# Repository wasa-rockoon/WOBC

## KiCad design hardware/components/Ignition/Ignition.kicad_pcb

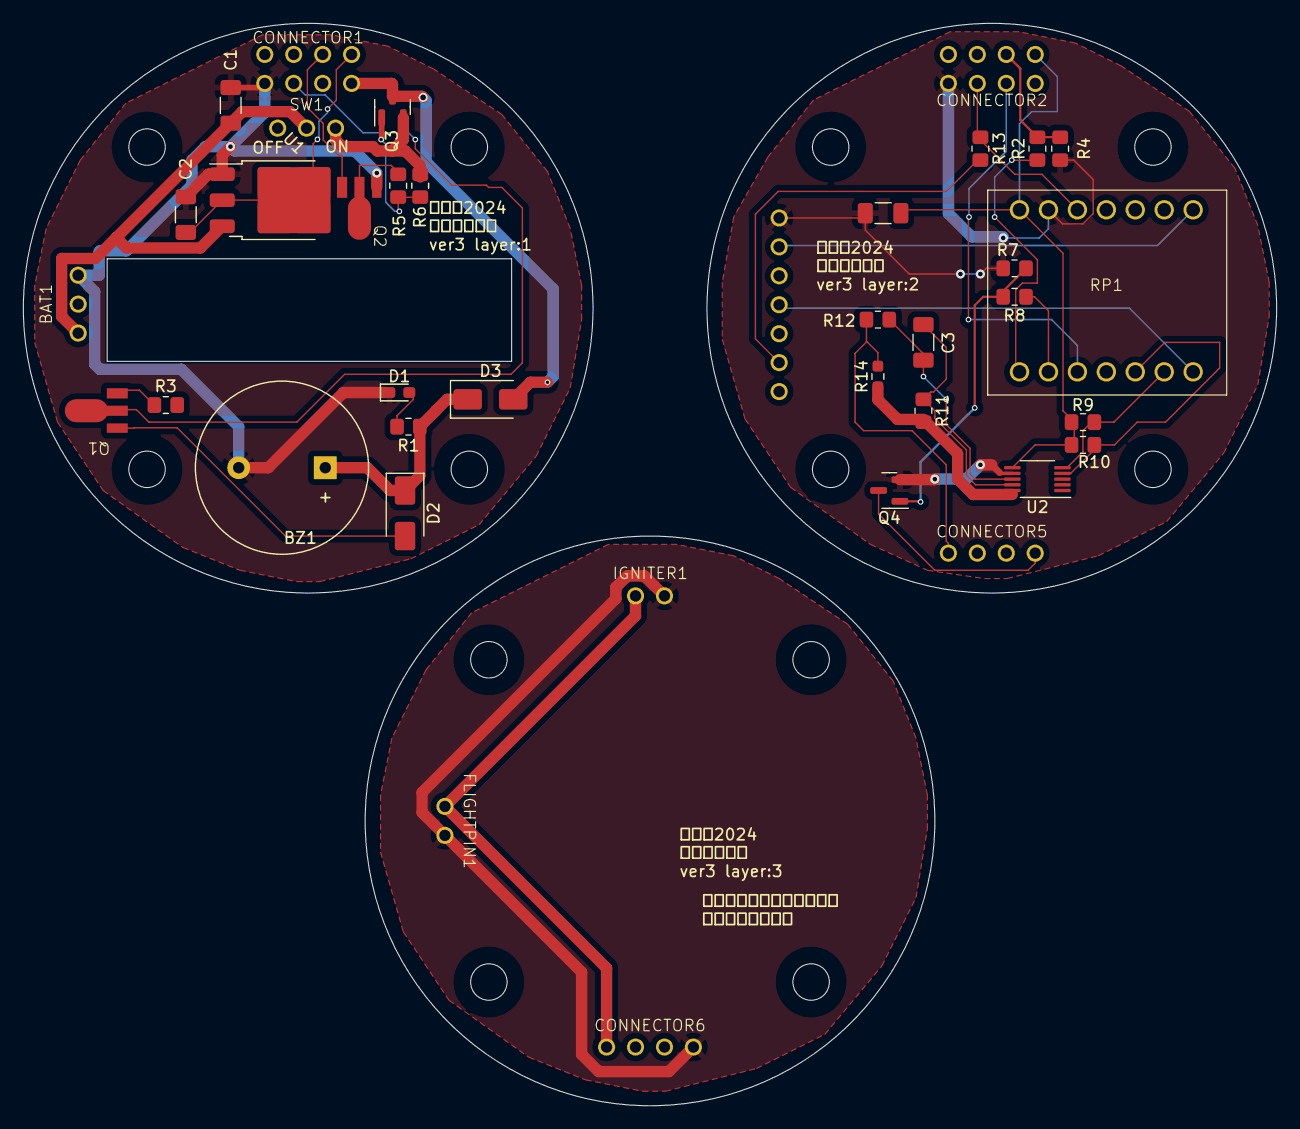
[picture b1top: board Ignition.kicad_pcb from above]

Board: 2 copper layers, 110.0 x 95.0 mm, 38 parts (0 on the bottom side), 33 nets.

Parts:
BAT1: 3pin_connector
BZ1: Buzzer; Buzzer_15x7.5RM7.6
C1, C2: 10μF; C_1206_3216Metric_Pad1.33x1.80mm_HandSolder
C3, C4: 0.1u; C_1206_3216Metric_Pad1.33x1.80mm_HandSolder
CONNECTOR1, CONNECTOR2: 8pin_looseconnector
CONNECTOR5, CONNECTOR6: 4pin_looseconnector
D1: LED; LED_0603_1608Metric_Pad1.05x0.95mm_HandSolder
D2, D3: US1M; D_SMA
FLIGHTPIN1: 2pin_connector
IGNITER1: 2pin_connector
Q1, Q2: NPN; npn
Q3: AO3401A; SOT-23
Q4: 2N7002; SOT-23
R1: 470; R_0805_2012Metric_Pad1.20x1.40mm_HandSolder
R2, R3, R7: 1000; R_0805_2012Metric_Pad1.20x1.40mm_HandSolder
R4, R6, R9, R10, R13: 10000; R_0805_2012Metric_Pad1.20x1.40mm_HandSolder
R5: 510; R_0805_2012Metric_Pad1.20x1.40mm_HandSolder
R8: 100; R_0805_2012Metric_Pad1.20x1.40mm_HandSolder
R11, R12: 4.7; R_0805_2012Metric_Pad1.20x1.40mm_HandSolder
R14: 0.002; R_0603_1608Metric_Pad0.98x0.95mm_HandSolder
RP1: SeeedXiaoRP2040
SW1: SW_DPDT_x2; SW
TWE1: TWELITE
U1: LM2940; TO-252-3_TabPin2
U2: INA226; VSSOP-10_3x3mm_P0.5mm

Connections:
/3V3_1: CONNECTOR1.7, Q1.1 (C)
/3V3_2: CONNECTOR2.7, R13.1, RP1.3 (3V3)
/ALART2: CONNECTOR2.6, RP1.12 (28)
/BAT1: Q3.2 (S), R6.1, SW1.3 (C)
/BAT1Z: CONNECTOR1.5, D3.2 (A), Q3.3 (D)
/BAT2: R11.2, R14.1, U2.10 (Vin+)
/BAT+: BAT1.1, C1.1, SW1.2 (B), U1.3 (I)
/GND1: BAT1.2, BZ1.2 (+), C1.2, C2.2, CONNECTOR1.8, D1.1 (K), Q2.3 (E), U1.1 (GND)
/GND2: C4.2, CONNECTOR2.8, Q4.2 (S), R4.2, R7.2, RP1.2 (GND), TWE1.1 (GND), U2.7 (GND)
/GND4: CONNECTOR6.4, FLIGHTPIN1.2, IGNITER1.2
/IGNITE+1: CONNECTOR1.3, Q2.2 (B)
/IGNITE+2: CONNECTOR2.3, R2.2, R4.1
/IGNITE-2: Q4.1 (G), R7.1, R8.2
/POW: C4.1, CONNECTOR2.4, R9.2, R10.2, RP1.1 (5V), U2.6 (VS)
/RX: RP1.7 (1), TWE1.2 (TXD)
/SCL: R9.1, RP1.9 (7), U2.5 (SCL)
/SDA: R10.1, RP1.10 (6), U2.4 (SDA)
/TX: RP1.8 (0), TWE1.4 (RXD)
unnamed: BZ1.1 (-), D2.1 (K), D3.1 (K), R1.1
unnamed: CONNECTOR5.1, R12.2, R14.2
unnamed: CONNECTOR6.1, FLIGHTPIN1.1, IGNITER1.1
unnamed: D1.2 (A), R1.2
unnamed: D2.2 (A), Q1.3 (E)
unnamed: Q1.2 (B), R3.1
unnamed: Q2.1 (C), R5.2
unnamed: Q3.1 (G), R5.1, R6.2
unnamed: CONNECTOR5.4, Q4.3 (D)
unnamed: R2.1, RP1.14 (26)
unnamed: R8.1, RP1.13 (27)
unnamed: R13.2, TWE1.6 (VCC)
unnamed: C2.1, CONNECTOR1.4, U1.2 (Q)
unnamed: C3.2, R12.1, U2.8 (Vbus)
unnamed: C3.1, R11.1, U2.9 (Vin-)

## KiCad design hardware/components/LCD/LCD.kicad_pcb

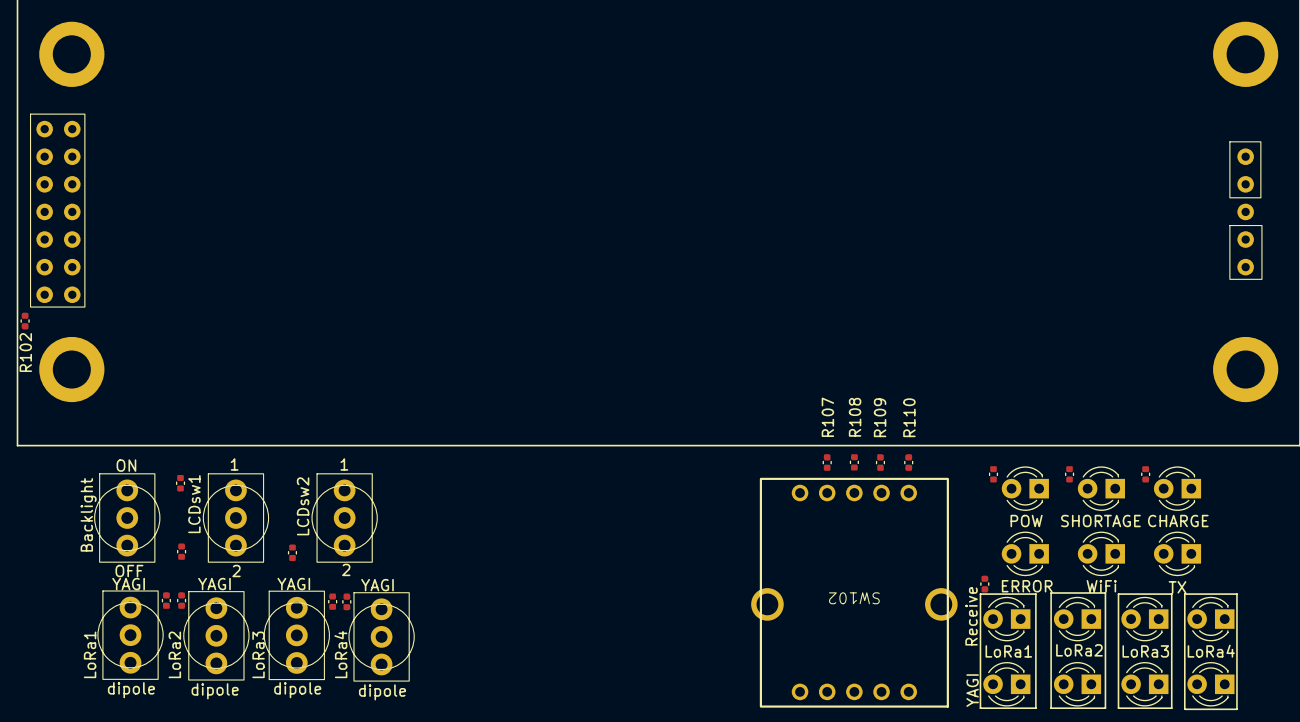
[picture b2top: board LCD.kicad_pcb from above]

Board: 2 copper layers, 40 parts (1 on the bottom side), 23 nets, no tracks yet.

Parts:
D101, D102, D103, D104, D105, D106, D107, D108, D109, D110, D111, D112, D113, D114: LED; LED_D3.0mm_FlatTop
J101: Conn_01x04_MountingPin; Grove_4P_L_SMD
R101, R107, R108, R109, R110, R111, R112, R113, R114, R115, R116: 47k; C_0402_1005Metric
R102, R103, R104, R105, R106: 1k; C_0402_1005Metric
SW101, SW103, SW104, SW105, SW106, SW107, SW108: sw1; ToggleSwitch
SW102: RotarySwitch_2x04
lcd101: SC2004CSWB-XA-LB-G; SC2004CSWB

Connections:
/LoRaSW1: R113.2, SW105.2 (B)
/LoRaSW2: R114.2, SW106.2 (B)
/LoRaSW3: R115.2, SW103.2 (B)
/LoRaSW4: R116.2, SW104.2 (B)
/ind_row1: D106.1 (K), D110.1 (K), D114.1 (K)
/ind_row2: D104.1 (K), D108.1 (K), D112.1 (K)
/ind_row3: D102.1 (K), D105.1 (K), D109.1 (K), D113.1 (K)
/ind_row4: D101.1 (K), D103.1 (K), D107.1 (K), D111.1 (K)
/launch_NoGo: J101.3, R107.2, SW102.2
/launch_abort: J101.2, R109.2, SW102.4
/launch_go: J101.1, R110.2, SW102.5
/launch_sub: R108.2, SW102.3
/lcd_sw1: R111.2, SW108.2 (B)
/lcd_sw2: R112.2, SW107.2 (B)
GND: J101.4, J101.MP (MountPin), R102.1, SW101.3 (C), SW102.1, SW103.3 (C), SW104.3 (C), SW105.3 (C), SW106.3 (C), SW107.3 (C), SW108.3 (C), lcd101.1 (VSS), lcd101.5 (R/W)
unnamed: D101.2 (A), D102.2 (A), R103.2
unnamed: D103.2 (A), D104.2 (A), D105.2 (A), D106.2 (A), R104.2
unnamed: D107.2 (A), D108.2 (A), D109.2 (A), D110.2 (A), R105.2
unnamed: D111.2 (A), D112.2 (A), D113.2 (A), D114.2 (A), R106.2
unnamed: R101.1, SW101.2 (B)
unnamed: R101.2, lcd101.17 (K)
unnamed: R102.2, lcd101.3 (Vo)
VDD: R107.1, R108.1, R109.1, R110.1, R111.1, R112.1, R113.1, R114.1, R115.1, R116.1, lcd101.2 (VDD), lcd101.15 (A)

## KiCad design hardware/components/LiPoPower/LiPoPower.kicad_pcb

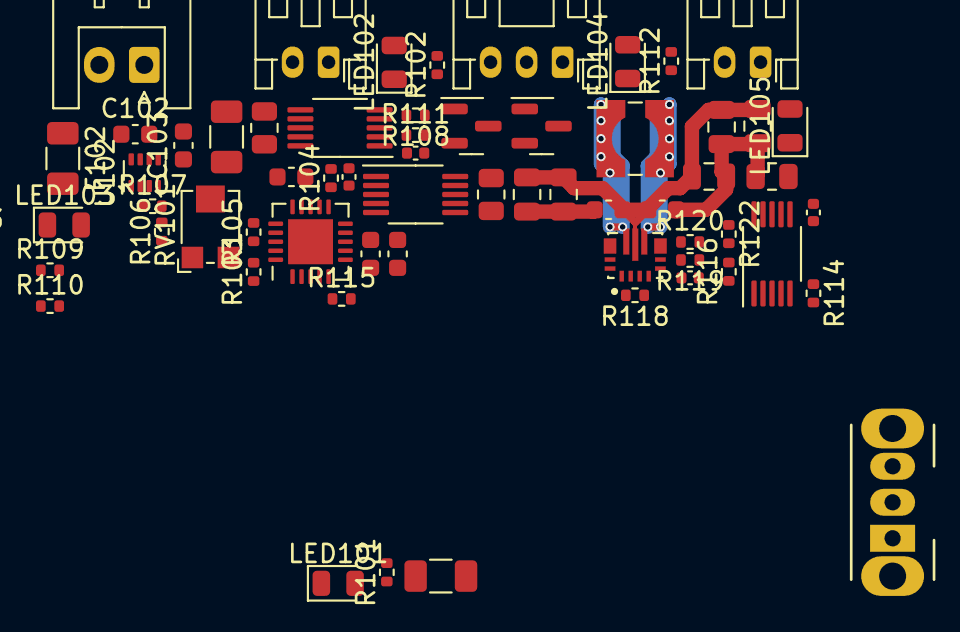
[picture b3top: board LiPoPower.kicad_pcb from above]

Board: 2 copper layers, 61 parts (0 on the bottom side), 36 nets.

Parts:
C101, C102, C103, C105, C106, C110, C112: 10uF; C_0603_1608Metric
C104, C109, C111, C116: 100nF; C_0402_1005Metric
C107, C108, C113, C114, C115: 22uF; C_0805_2012Metric
F101, F102, F103: Polyfuse; Fuse_1206_3216Metric
J101: Battery; JST_XH_S2B-XH-A_1x02_P2.50mm_Horizontal
J102: Temp&Heater; JST_PH_S3B-PH-K_1x03_P2.00mm_Horizontal
J103: Ext Switch; JST_PH_S2B-PH-K_1x02_P2.00mm_Horizontal
J104: LiPo; JST_PH_S2B-PH-K_1x02_P2.00mm_Horizontal
L101: L; L_Wuerth_WE-TPC-3816
LED101: USB Power; LED_0805_2012Metric
LED102: CHARGE; LED_0805_2012Metric
LED103: Backup; LED_0805_2012Metric
LED104: Heater; LED_0805_2012Metric
LED105: VDD; LED_0805_2012Metric
Q101: Q_NPN_BEC; SOT-23
Q102: Q_PMOS_GSD; SOT-23
R101, R102, R103, R109, R112, R122: 1k; R_0402_1005Metric
R104, R105, R107, R110, R118: 100k; R_0402_1005Metric
R106, R120: 47k; R_0402_1005Metric
R108, R111, R114, R115: 10k; R_0402_1005Metric
R113, R117, R121: 50mΩ; R_0805_2012Metric
R116: 330k; R_0402_1005Metric
R119: 15k; R_0402_1005Metric
RV101: 10k; Potentiometer_Bourns_TC33X_Vertical
SW101: Power Switch; SW_CuK_OS102011MA1QN1_SPDT_Angled
U101: MCP73871-1CC; QFN-20-1EP_4x4mm_P0.5mm_EP2.5x2.5mm
U102: TPS2116DRL; SOT-583-8
U103, U104, U106: INA226; VSSOP-10_3x3mm_P0.5mm
U105: TPS63070RNMR; VREG_TPS63070RNMR

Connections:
/I2C_SCL: U103.1 (A1), U103.5 (SCL), U104.1 (A1), U104.2 (A0), U104.5 (SCL), U106.1 (A1), U106.5 (SCL)
/I2C_SDA: U103.4 (SDA), U104.4 (SDA), U106.2 (A0), U106.4 (SDA)
/PROG: RV101.2, U101.13 (PROG1)
/ST: R109.2, U102.8 (ST)
/TEMP: J102.2, R115.1, U101.5 (THERM)
/VDD_BUS: C112.1, C113.1, C114.1, C115.1, C116.1, R118.1, R120.2, R121.1, U105.7_8 (VOUT), U106.6 (VS), U106.8 (Vbus), U106.10 (Vin+)
GND: C101.2, C102.2, C103.2, C104.2, C105.2, C106.2, C107.2, C108.2, C109.2, C110.2, C111.2, C112.2, C113.2, C114.2, C115.2, C116.2, J101.2, J102.3, J104.2, LED102.1 (K), Q101.2 (E), R101.2, R103.2, R104.2, R106.1, R110.2, R112.1, R115.2, R116.2, R119.1, R122.2, U101.9 (~TE), U101.10 (V_{SS}), U101.11 (V_{SS}), U101.21 (V_{SS}), U102.1 (GND), U103.7 (GND), U104.7 (GND), U105.4 (GND), U105.10 (PGND), U105.15 (VSEL), U106.7 (GND)
unnamed: F102.1, J101.1
unnamed: J102.1, LED104.2 (A), Q102.3 (D)
unnamed: J103.1, R114.1, SW101.2 (B)
unnamed: J103.2, R116.1, SW101.3 (C), U103.3 (~Alert), U105.1 (PS/SYNC), U105.14 (EN), U106.3 (~Alert)
unnamed: F103.2, J104.1
unnamed: C101.1, F101.2, LED101.2 (A), R105.1, U101.2 (VPCC), U101.3 (SEL), U101.18 (IN), U101.19 (IN)
unnamed: LED101.1 (K), R101.1
unnamed: LED102.2 (A), R102.1
unnamed: LED103.1 (K), R109.1
unnamed: LED104.1 (K), R112.2
unnamed: LED105.1 (K), R122.1
unnamed: Q101.1 (B), R108.1, R110.1
unnamed: Q101.3 (C), Q102.1 (G), R111.2
unnamed: R103.1, RV101.3
unnamed: R105.2, U101.17 (CE), U104.3 (~Alert)
unnamed: R104.1, U101.12 (PROG3)
unnamed: C106.1, R117.1, U101.14 (V_{BAT}), U101.15 (V_{BAT}), U101.16 (V_{BAT_SENSE}), U104.9 (Vin-)
unnamed: C103.1, C105.1, R107.1, U101.1 (OUT), U101.20 (OUT), U102.3 (VIN1), U102.5 (MODE)
unnamed: R106.2, R107.2, U102.4 (PR1)
unnamed: C102.1, F102.2, U102.6 (VIN2)
unnamed: C107.1, C108.1, C110.1, R113.2, R114.2, U103.9 (Vin-), U105.12_13 (VIN)
unnamed: F103.1, R117.2, U104.8 (Vbus), U104.10 (Vin+)
unnamed: R119.2, R120.1, U105.5 (FB)
unnamed: L101.1, U105.11 (L1)
unnamed: L101.2, U105.9 (L2)
unnamed: R118.2, U105.2 (PG)
unnamed: C111.1, U105.3 (VAUX)
VDD: LED105.2 (A), R121.2, U106.9 (Vin-)
VPP: C104.1, C109.1, LED103.2 (A), Q102.2 (S), R111.1, R113.1, U102.2 (VOUT), U102.7 (VOUT), U103.2 (A0), U103.6 (VS), U103.10 (Vin+), U104.6 (VS)

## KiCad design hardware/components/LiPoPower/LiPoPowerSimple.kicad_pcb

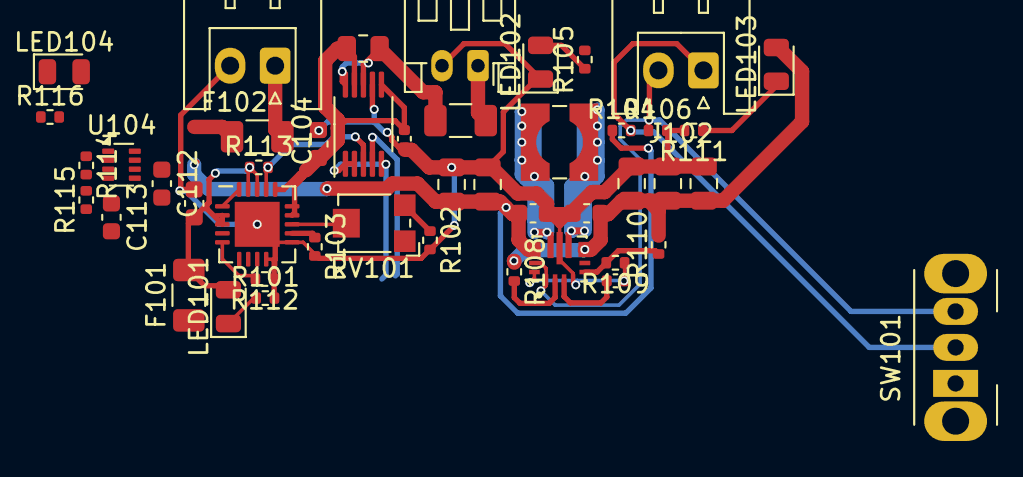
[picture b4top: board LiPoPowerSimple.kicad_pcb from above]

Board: 2 copper layers, 46 parts (0 on the bottom side), 29 nets.

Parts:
C101, C104, C105, C108, C112, C113: 10uF; C_0603_1608Metric
C102, C103, C109, C110, C111: 10uF; C_0805_2012Metric
C106, C107: 100nF; C_0402_1005Metric
F101, F102, F103: Polyfuse; Fuse_1206_3216Metric
J101: Battery; JST_XH_S2B-XH-A_1x02_P2.50mm_Horizontal
J102: Ext Switch; JST_XH_S2B-XH-A_1x02_P2.50mm_Horizontal
J103: LiPo; JST_PH_S2B-PH-K_1x02_P2.00mm_Horizontal
L101: L; L_Wuerth_WE-TPC-3816
LED101: USB Power; LED_0805_2012Metric
LED102: CHARGE; LED_0805_2012Metric
LED103: VDD; LED_0805_2012Metric
LED104: Backup; LED_0805_2012Metric
R101, R102, R105, R111, R116: 1k; R_0402_1005Metric
R103, R106, R108, R113, R115: 100k; R_0402_1005Metric
R104, R112: 10k; R_0402_1005Metric
R107: 50mΩ; R_0805_2012Metric
R109: 15k; R_0402_1005Metric
R110, R114: 47k; R_0402_1005Metric
RV101: 10k; Potentiometer_Bourns_TC33X_Vertical
SW101: Power Switch; SW_Slide_SPDT_Angled_CK_OS102011MA1Q
U101: MCP73871-1CC; QFN-20-1EP_4x4mm_P0.5mm_EP2.5x2.5mm
U102: TPS63070RNMR; VREG_TPS63070RNMR
U103: INA226; VSSOP-10_3x3mm_P0.5mm
U104: TPS2116DRL; SOT-583-8

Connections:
/I2C_SCL: U103.1 (A1), U103.2 (A0), U103.5 (SCL)
/ST: R116.2, U104.8 (ST)
GND: C101.2, C102.2, C103.2, C104.2, C105.2, C106.2, C107.2, C108.2, C109.2, C110.2, C111.2, C112.2, C113.2, J101.2, J103.2, LED102.1 (K), R101.2, R102.2, R103.2, R106.2, R109.1, R111.2, R112.1, R114.1, U101.9 (~TE), U101.10 (V_{SS}), U101.11 (V_{SS}), U101.21 (V_{SS}), U102.4 (GND), U102.10 (PGND), U102.15 (VSEL), U103.7 (GND), U104.1 (GND)
unnamed: F102.1, J101.1
unnamed: J102.1, R104.2, SW101.2 (B)
unnamed: J102.2, R106.1, SW101.3 (C), U102.1 (PS/SYNC), U102.14 (EN)
unnamed: F103.2, J103.1
unnamed: C101.1, F101.2, LED101.2 (A), R113.1, U101.2 (VPCC), U101.3 (SEL), U101.18 (IN), U101.19 (IN)
unnamed: LED101.1 (K), R101.1
unnamed: LED102.2 (A), R105.1
unnamed: LED103.1 (K), R111.1
unnamed: C102.1, C103.1, C105.1, C106.1, LED104.2 (A), R104.1, U102.12_13 (VIN), U103.6 (VS), U104.2 (VOUT), U104.7 (VOUT)
unnamed: LED104.1 (K), R116.1
unnamed: R102.1, RV101.3
unnamed: R113.2, U101.17 (CE), U103.3 (~Alert)
unnamed: RV101.2, U101.13 (PROG1)
unnamed: R103.1, U101.12 (PROG3)
unnamed: R112.2, U101.5 (THERM)
unnamed: C104.1, R107.1, U101.14 (V_{BAT}), U101.15 (V_{BAT}), U101.16 (V_{BAT_SENSE}), U103.9 (Vin-)
unnamed: R109.2, R110.1, U102.5 (FB)
unnamed: L101.1, U102.11 (L1)
unnamed: L101.2, U102.9 (L2)
unnamed: R108.2, U102.2 (PG)
unnamed: C107.1, U102.3 (VAUX)
unnamed: F103.1, R107.2, U103.8 (Vbus), U103.10 (Vin+)
unnamed: C113.1, R115.1, U101.1 (OUT), U101.20 (OUT), U104.3 (VIN1), U104.5 (MODE)
unnamed: R114.2, R115.2, U104.4 (PR1)
unnamed: C112.1, F102.2, U104.6 (VIN2)
VDD: C108.1, C109.1, C110.1, C111.1, LED103.2 (A), R108.1, R110.2, U102.7_8 (VOUT)

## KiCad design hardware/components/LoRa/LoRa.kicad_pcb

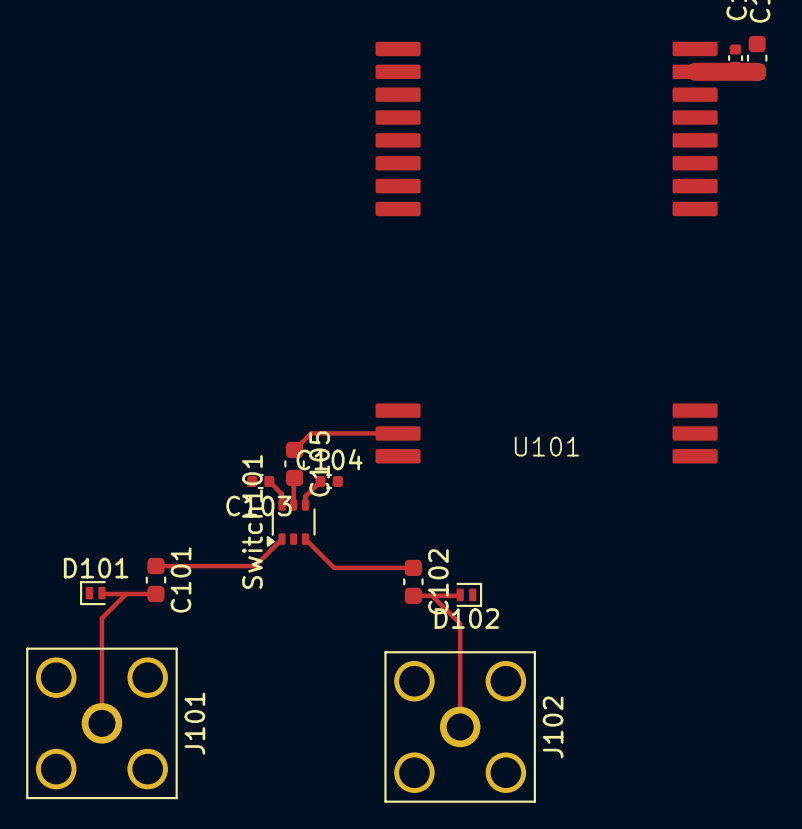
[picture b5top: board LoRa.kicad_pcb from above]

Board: 2 copper layers, 13 parts (0 on the bottom side), 10 nets.

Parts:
C101, C102, C105: 100p; C_0603_1608Metric
C103, C104, C107: 100n; C_0402_1005Metric
C106: 10u; C_0603_1608Metric
D101, D102: ESD9B5.0ST5G; D_SOD-882
J101, J102: SMA; SMA_Amphenol_132203-12_Horizontal
Switch101: XA17-G4K1; SOT-363_SC-70-6
U101: E220-900T22S(JP)

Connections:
/RF_switch1: C103.1, Switch101.6 (V2)
/RF_switch2: C104.1, Switch101.4 (V1)
GND: C103.2, C104.2, C106.2, C107.2, D101.1 (A1), D102.1 (A1), J101.2 (Ext), J102.2 (Ext), Switch101.2 (GND), U101.1 (GND), U101.2 (GND), U101.3 (GND), U101.4 (GND), U101.11 (GND), U101.13 (GND), U101.19 (GND), U101.20 (GND), U101.22 (GND)
unnamed: C101.2, D101.2 (A2), J101.1 (In)
unnamed: C102.2, D102.2 (A2), J102.1 (In)
unnamed: C105.2, Switch101.5 (J1)
unnamed: C102.1, Switch101.3 (J2)
unnamed: C101.1, Switch101.1 (J3)
unnamed: C105.1, U101.21 (ANT)
VDD: C106.1, C107.1, U101.10 (VDD)

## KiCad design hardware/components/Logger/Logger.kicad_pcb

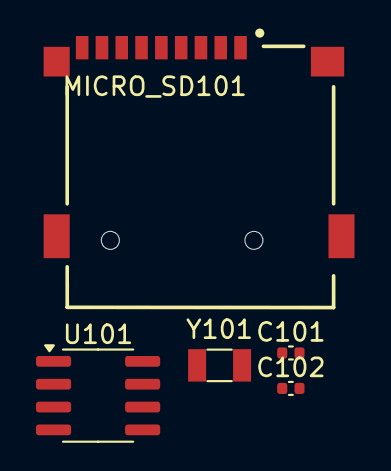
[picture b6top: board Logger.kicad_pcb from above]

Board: 2 copper layers, 5 parts (0 on the bottom side), 5 nets, no tracks yet.

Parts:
C101: 10uF; C_0402_1005Metric
C102: 100nF; C_0402_1005Metric
MICRO_SD101: TF-01A
U101: PCF8563T; SOIC-8_3.9x4.9mm_P1.27mm
Y101: Crystal; Crystal_SMD_3215-2Pin_3.2x1.5mm

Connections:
+BATT: C102.2, U101.8 (VDD)
GND: C101.2, C102.1, MICRO_SD101.6 (VSS), MICRO_SD101.MP1 (SHIELD), MICRO_SD101.MP2 (SHIELD), MICRO_SD101.MP3 (SHIELD), MICRO_SD101.MP4 (SHIELD), U101.4 (VSS)
unnamed: U101.1 (OSCI), Y101.1
unnamed: U101.2 (OSCO), Y101.2
VDD: C101.1, MICRO_SD101.4 (VDD)

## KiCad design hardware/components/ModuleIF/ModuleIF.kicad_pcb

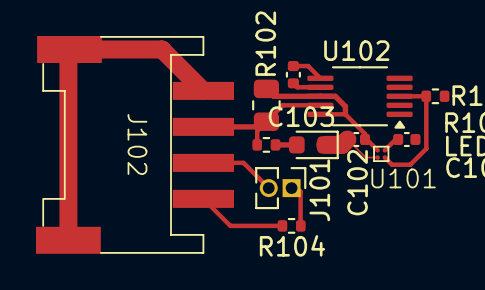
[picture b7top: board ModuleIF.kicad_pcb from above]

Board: 2 copper layers, 12 parts (0 on the bottom side), 11 nets.

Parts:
C101, C102, C103: 100nF; C_0402_1005Metric
J101: Jumper; PinHeader_1x02_P1.27mm_Vertical
J102: Conn_01x04_MountingPin; Grove_4P_L_SMD
LED101: Power; LED_0603_1608Metric
R101: 10k; R_0402_1005Metric
R102: 50mΩ; R_0805_2012Metric
R103: 1k; R_0402_1005Metric
R104: 120; R_0402_1005Metric
U101: TCK106AF; WCSPD-4(0.8x0.8)
U102: INA226; VSSOP-10_3x3mm_P0.5mm

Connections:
/CANH: J102.1, R104.2
/CANL: J101.2, J102.2
/I2C_SDA: U102.1 (A1), U102.4 (SDA)
/VIN: C101.2, U101.5 (VIN)
GND: C101.1, C102.1, C103.1, J102.4, J102.MP (MountPin), LED101.1 (K), U101.2 (GND), U102.7 (GND)
unnamed: J101.1, R104.1
unnamed: J102.3, R102.2, R103.2, U102.9 (Vin-)
unnamed: LED101.2 (A), R103.1
unnamed: R101.2, U101.3 (CONTROL), U102.3 (~Alert)
unnamed: C102.2, R102.1, U101.1 (VOUT), U102.8 (Vbus), U102.10 (Vin+)
VDD: C103.2, U102.6 (VS)

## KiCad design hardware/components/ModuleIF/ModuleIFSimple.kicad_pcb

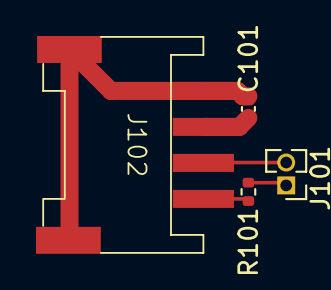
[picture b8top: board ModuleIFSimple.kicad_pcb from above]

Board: 2 copper layers, 4 parts (0 on the bottom side), 5 nets.

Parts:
C101: 100nF; C_0402_1005Metric
J101: Jumper; PinHeader_1x02_P1.27mm_Vertical
J102: Conn_01x04_MountingPin; Grove_4P_L_SMD
R101: 120; R_0402_1005Metric

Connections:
/CANH: J102.1, R101.2
/CANL: J101.2, J102.2
/VIO: C101.2, J102.3
GND: C101.1, J102.4, J102.MP (MountPin)
unnamed: J101.1, R101.1
